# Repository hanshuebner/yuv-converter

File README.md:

# YUV to RGB converter

This is a converter circuit originally for the Sinclair ZX spectrum,
found on
https://k1.spdns.de/Vintage/Sinclair/82/Doityourself/YUV%20to%20RGB%20converter%20%5BPera%20Putnik%5D/uvyrgb.htm

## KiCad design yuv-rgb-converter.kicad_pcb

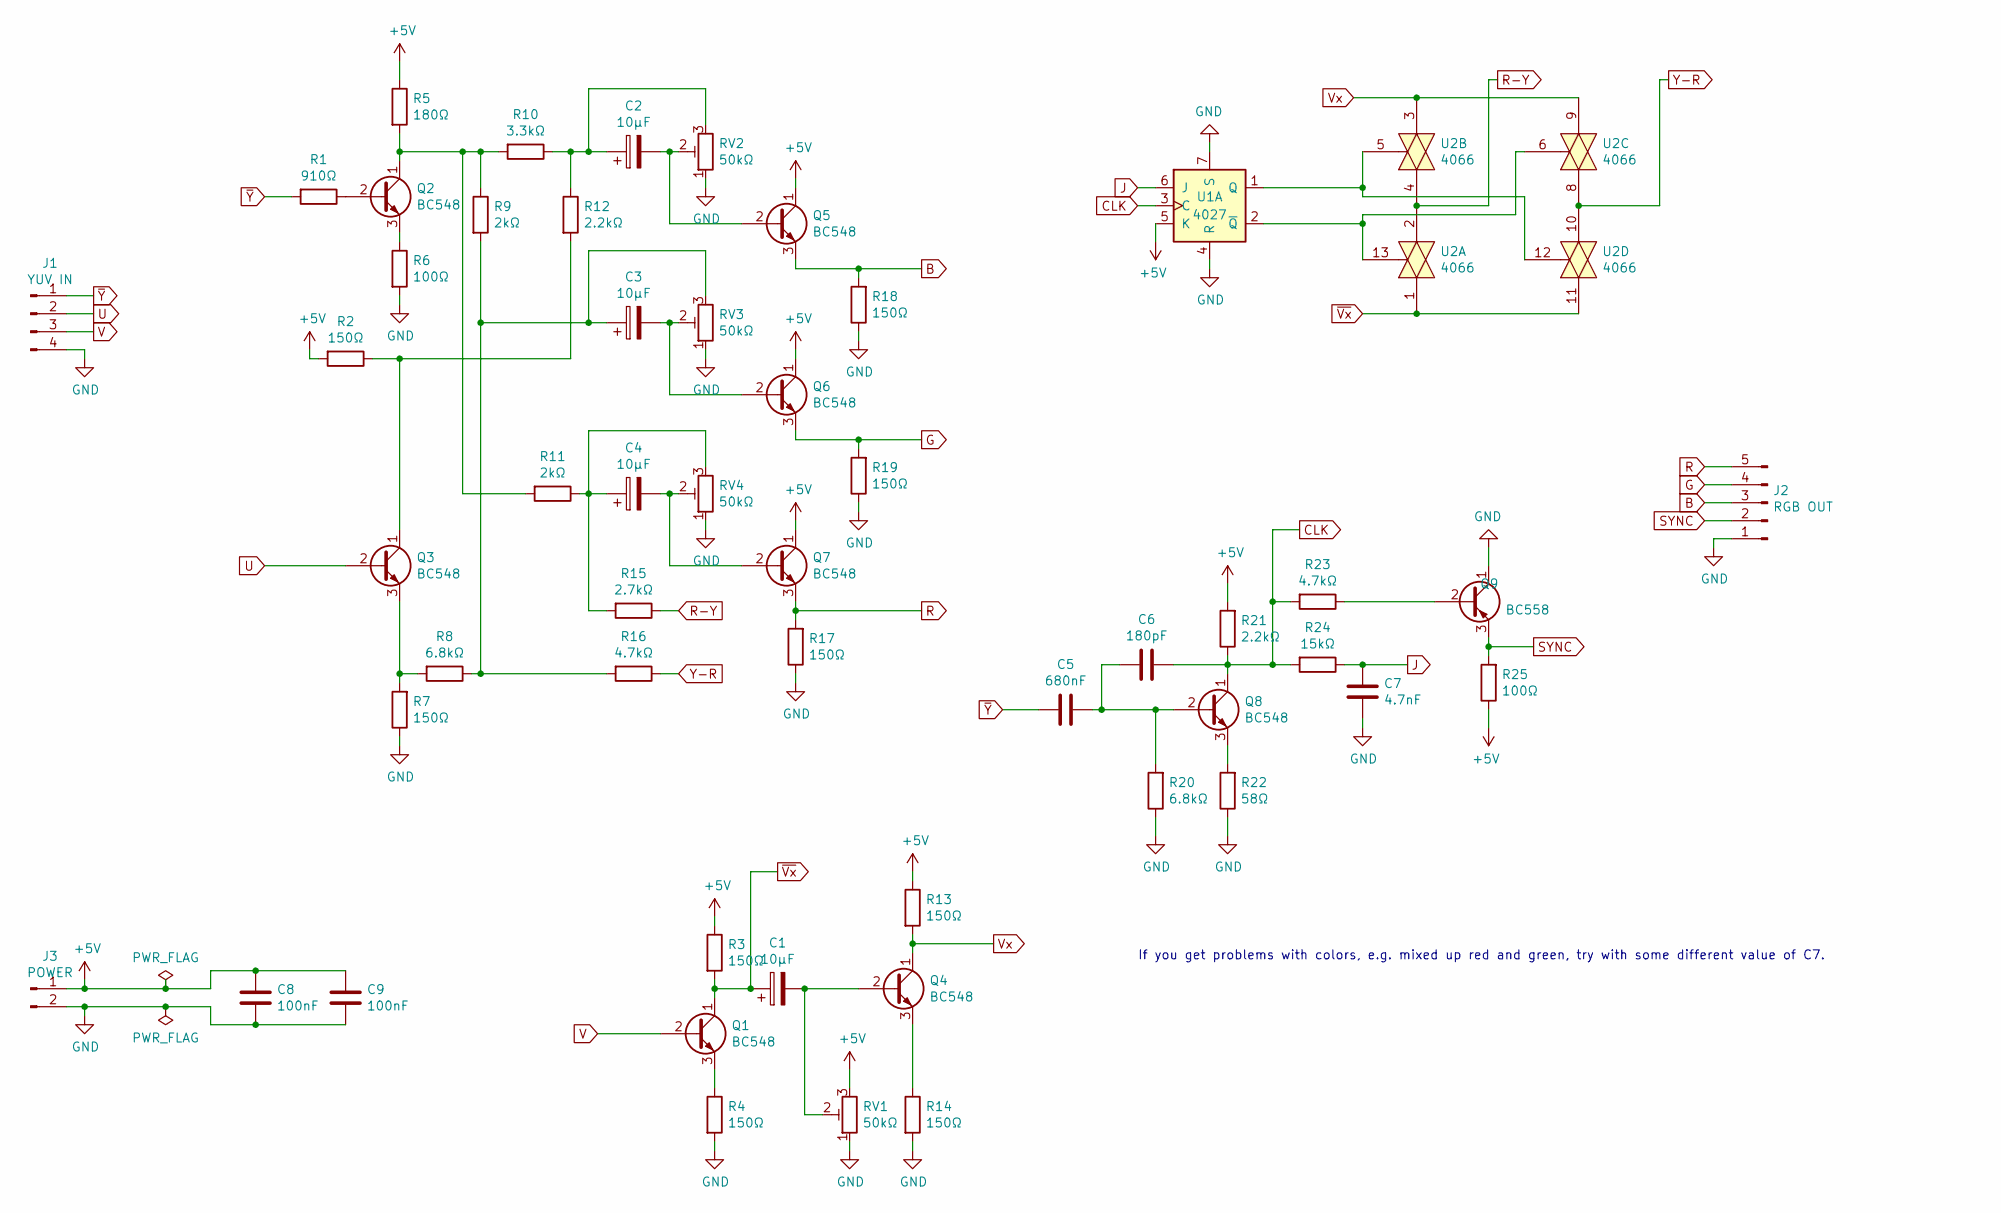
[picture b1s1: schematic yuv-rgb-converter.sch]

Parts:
C1, C2, C3, C4: 10µF; C_0805_2012Metric_Pad1.15x1.40mm_HandSolder
C5: 680nF; C_0805_2012Metric_Pad1.15x1.40mm_HandSolder
C6: 180pF; C_0805_2012Metric_Pad1.15x1.40mm_HandSolder
C7: 4.7nF; C_0805_2012Metric_Pad1.15x1.40mm_HandSolder
C8, C9: 100nF; C_0805_2012Metric_Pad1.15x1.40mm_HandSolder
J1: YUV IN; PinHeader_1x04_P2.54mm_Vertical
J2: RGB OUT; PinHeader_1x05_P2.54mm_Vertical
J3: POWER; PinHeader_1x02_P2.54mm_Vertical
Q1, Q2, Q3, Q4, Q5, Q6, Q7, Q8: BC548; TO-92_Inline
Q9: BC558; TO-92_Inline
R1: 910Ω; R_0805_2012Metric_Pad1.15x1.40mm_HandSolder
R2, R3, R4, R7, R13, R14, R17, R18, R19: 150Ω; R_0805_2012Metric_Pad1.15x1.40mm_HandSolder
R5: 180Ω; R_0805_2012Metric_Pad1.15x1.40mm_HandSolder
R6, R25: 100Ω; R_0805_2012Metric_Pad1.15x1.40mm_HandSolder
R8, R20: 6.8kΩ; R_0805_2012Metric_Pad1.15x1.40mm_HandSolder
R9, R11: 2kΩ; R_0805_2012Metric_Pad1.15x1.40mm_HandSolder
R10: 3.3kΩ; R_0805_2012Metric_Pad1.15x1.40mm_HandSolder
R12, R21: 2.2kΩ; R_0805_2012Metric_Pad1.15x1.40mm_HandSolder
R15: 2.7kΩ; R_0805_2012Metric_Pad1.15x1.40mm_HandSolder
R16, R23: 4.7kΩ; R_0805_2012Metric_Pad1.15x1.40mm_HandSolder
R22: 58Ω; R_0805_2012Metric_Pad1.15x1.40mm_HandSolder
R24: 15kΩ; R_0805_2012Metric_Pad1.15x1.40mm_HandSolder
RV1, RV2, RV3, RV4: 50kΩ; Potentiometer_Piher_PT-6-V_Vertical
U1: 4027; DIP-16_W7.62mm_Socket
U2: 4066; DIP-14_W7.62mm_Socket

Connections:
+5V: C8.2, C9.2, J3.1, Q5.1 (C), Q6.1 (C), Q7.1 (C), R2.2, R3.1, R5.1, R13.1, R21.2, R25.1, RV1.3, U1.5 (K), U1.16 (VDD), U2.14 (VDD)
B: J2.3, Q5.3 (E), R18.2
CLK: C6.1, Q8.1 (C), R21.1, R23.2, R24.2, U1.3 (C)
G: J2.4, Q6.3 (E), R19.2
GND: C7.1, C8.1, C9.1, J1.4, J2.1, J3.2, Q9.1 (C), R4.2, R6.2, R7.1, R14.2, R17.1, R18.1, R19.1, R20.1, R22.1, RV1.1, RV2.1, RV3.1, RV4.1, U1.4 (R), U1.7 (S), U1.8 (VSS), U2.7 (VSS)
J: C7.2, R24.1, U1.6 (J)
unnamed: C1.2, Q4.2 (B), RV1.2
unnamed: C2.1, R10.1, R12.1, RV2.3
unnamed: C2.2, Q5.2 (B), RV2.2
unnamed: C3.1, R8.1, R9.2, R16.2, RV3.3
unnamed: C3.2, Q6.2 (B), RV3.2
unnamed: C4.1, R11.1, R15.2, RV4.3
unnamed: C4.2, Q7.2 (B), RV4.2
unnamed: C5.1, C6.2, Q8.2 (B), R20.2
unnamed: Q1.3 (E), R4.1
unnamed: Q2.1 (C), R5.2, R9.1, R10.2, R11.2
unnamed: Q2.2 (B), R1.1
unnamed: Q2.3 (E), R6.1
unnamed: Q3.1 (C), R2.1, R12.2
unnamed: Q3.3 (E), R7.2, R8.2
unnamed: Q4.3 (E), R14.1
unnamed: Q8.3 (E), R22.2
unnamed: Q9.2 (B), R23.1
unnamed: U1.1 (Q), U2.5, U2.12
unnamed: U1.2 (~Q), U2.6, U2.13
R: J2.5, Q7.3 (E), R17.2
R-Y: R15.1, U2.2, U2.4
SYNC: J2.2, Q9.3 (E), R25.2
U: J1.2, Q3.2 (B)
V: J1.3, Q1.2 (B)
Vx: Q4.1 (C), R13.2, U2.3, U2.9
Y-R: R16.1, U2.8, U2.10
~Vx: C1.1, Q1.1 (C), R3.2, U2.1, U2.11
~Y: C5.2, J1.1, R1.2

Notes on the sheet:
If you get problems with colors, e.g. mixed up red and green, try with some different value of C7.

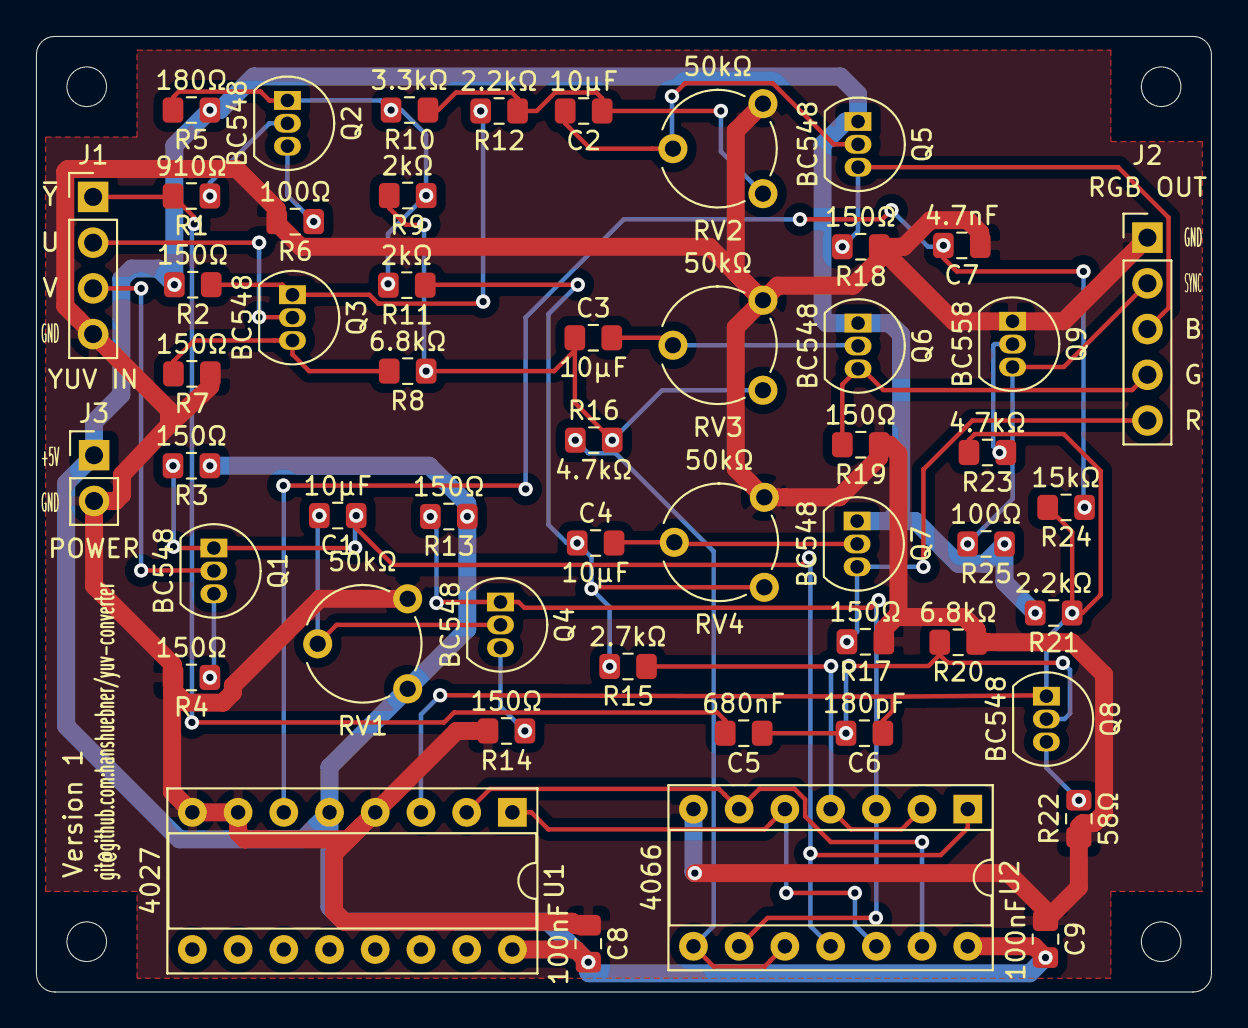
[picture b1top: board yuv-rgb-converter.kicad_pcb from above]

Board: 2 copper layers, 65.3 x 53.1 mm, 52 parts (0 on the bottom side), 34 nets.

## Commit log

2020-06-04 Checkpoint #1
2020-06-04 clean up
2020-06-04 README, original schematics
2020-06-04 Production files & PDF
2020-06-04 Sent to JLCPCB
